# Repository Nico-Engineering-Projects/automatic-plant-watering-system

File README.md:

# Automatic Plant Watering System

An engineering project by Nico Gerber to develop an ESP32-based system that measures soil moisture and controls a water pump.

**Status:** In progress — breadboard assembly and development planning.

## Goal

Develop the hardware and firmware step by step, verify each stage, and document the design decisions, measurements and lessons learned.

## Current progress

- Relay and pump connected on the breadboard.
- ESP32 board selection, GPIO assignment, relay behaviour and electrical connections still need to be recorded and verified.
- Firmware development and functional testing are next.
- No watering performance or reliability results have been established yet.

## Planned development phases

- [ ] Verify ESP32 upload and Serial Monitor communication.
- [ ] Verify relay control and startup state with the pump disconnected.
- [ ] Verify a deliberately triggered short pump run with automatic shutoff.
- [ ] Measure and calibrate the soil-moisture sensor.
- [ ] Implement and test automatic watering with a soak period.
- [ ] Evaluate the results and document improvements.

## Planned software tools

- Visual Studio Code
- PlatformIO IDE
- Arduino framework for ESP32
- Git and GitHub for version history

The exact ESP32 board and GPIO configuration will be documented before the first firmware is added.

## Documentation

- [Development log](docs/development-log.md)
- Circuit diagrams, component list and test results will be added as the project progresses.
- The Word project report will be kept in `docs/`; a readable PDF can be included with major milestones.

## Project structure as the work grows

| Location | Contents |
| --- | --- |
| `README.md` | Current overview, status and setup instructions |
| `src/` | Firmware source, added when the PlatformIO project is created |
| `platformio.ini` | Verified board, framework and build configuration |
| `hardware/` | Wiring diagrams, schematics and parts list |
| `docs/` | Development log and project report |
| `results/` | Measurements and test observations |
| `images/` | Photographs of the actual project |

## Development history

Small changes are recorded as commits. Tags and releases will mark verified milestones. Each log entry should record what was actually tested and link to the relevant commit.

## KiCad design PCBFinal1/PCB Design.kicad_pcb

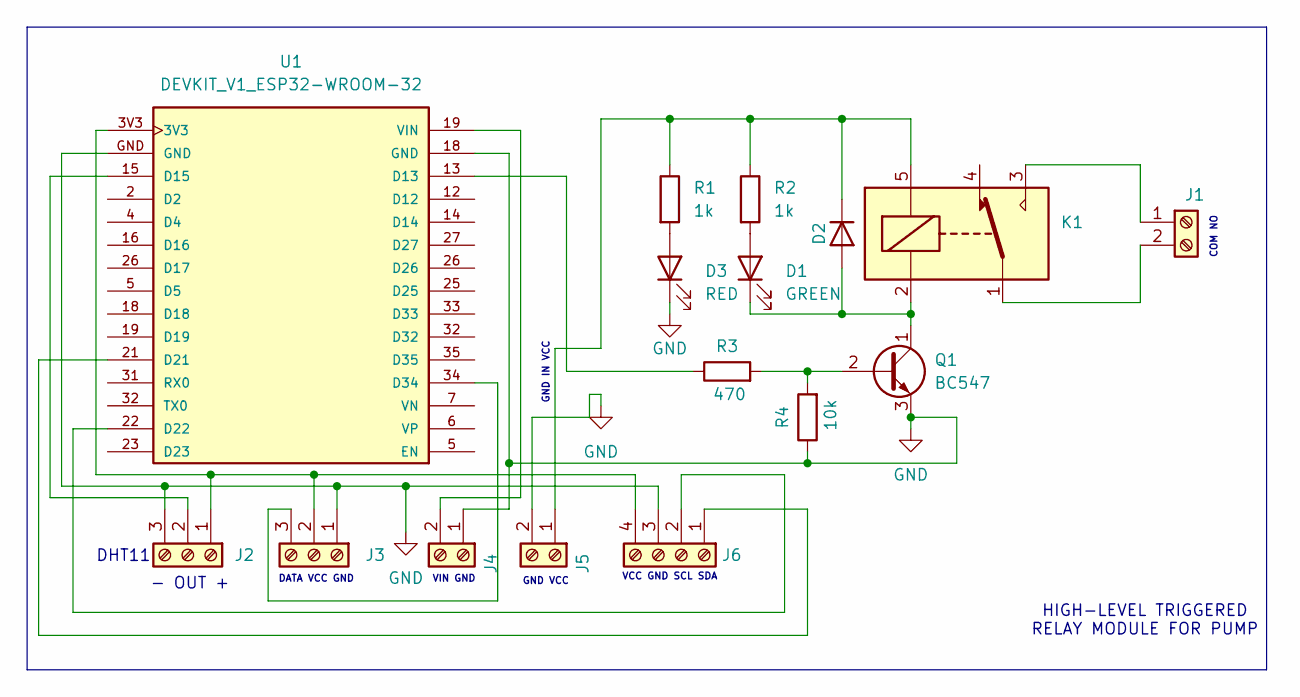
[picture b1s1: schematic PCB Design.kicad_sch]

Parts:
D1: GREEN; LED_D5.0mm
D2: 1N4007; D_DO-41_SOD81_P10.16mm_Horizontal
D3: RED; LED_D5.0mm
J1, J4, J5: Screw_Terminal_01x02; TerminalBlock_Phoenix_MKDS-1,5-2_1x02_P5.00mm_Horizontal
J2, J3: Screw_Terminal_01x03; TerminalBlock_Phoenix_MKDS-1,5-3-5.08_1x03_P5.08mm_Horizont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
J6: Screw_Terminal_01x04; TerminalBlock_Phoenix_MKDS-1,5-4-5.08_1x04_P5.08mm_Horizont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
K1: SANYOU_SRD_Form_C; Relay_SPDT_SANYOU_SRD_Series_Form_C
Q1: BC547; TO-92_Inline
R1, R2: 1k; R_Axial_DIN0207_L6.3mm_D2.5mm_P7.62mm_Horizontal
R3: 470; R_Axial_DIN0207_L6.3mm_D2.5mm_P7.62mm_Horizontal
R4: 10k; R_Axial_DIN0207_L6.3mm_D2.5mm_P7.62mm_Horizontal
U1: DEVKIT_V1_ESP32-WROOM-32; MODULE_DEVKIT_V1_ESP32-WROOM-32; PARTREV N/A

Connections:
GND: D3.1 (K), J2.3, J3.1, J4.1, J5.2, J6.3, Q1.3 (E), R4.1, U1.18 (GND), U1.GND
unnamed: D1.2 (A), R2.2
unnamed: D1.1 (K), D2.2 (A), K1.2, Q1.1 (C)
unnamed: D2.1 (K), J5.1, K1.5, R1.1, R2.1
unnamed: D3.2 (A), R1.2
unnamed: J1.1, K1.3
unnamed: J1.2, K1.1
unnamed: J2.1, J3.2, J6.4, U1.3V3
unnamed: J2.2, U1.15 (D15)
unnamed: J3.3, U1.34 (D34)
unnamed: J4.2, U1.19 (VIN)
unnamed: J6.1, U1.21 (D21)
unnamed: J6.2, U1.22 (D22)
unnamed: Q1.2 (B), R3.2, R4.2
unnamed: R3.1, U1.13 (D13)

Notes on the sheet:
DHT11
GND VCC
DATA VCC GND
GND IN VCC
COM NO
VIN GND
HIGH-LEVEL TRIGGERED RELAY MODULE FOR PUMP
VCC GND SCL SDA
- OUT +

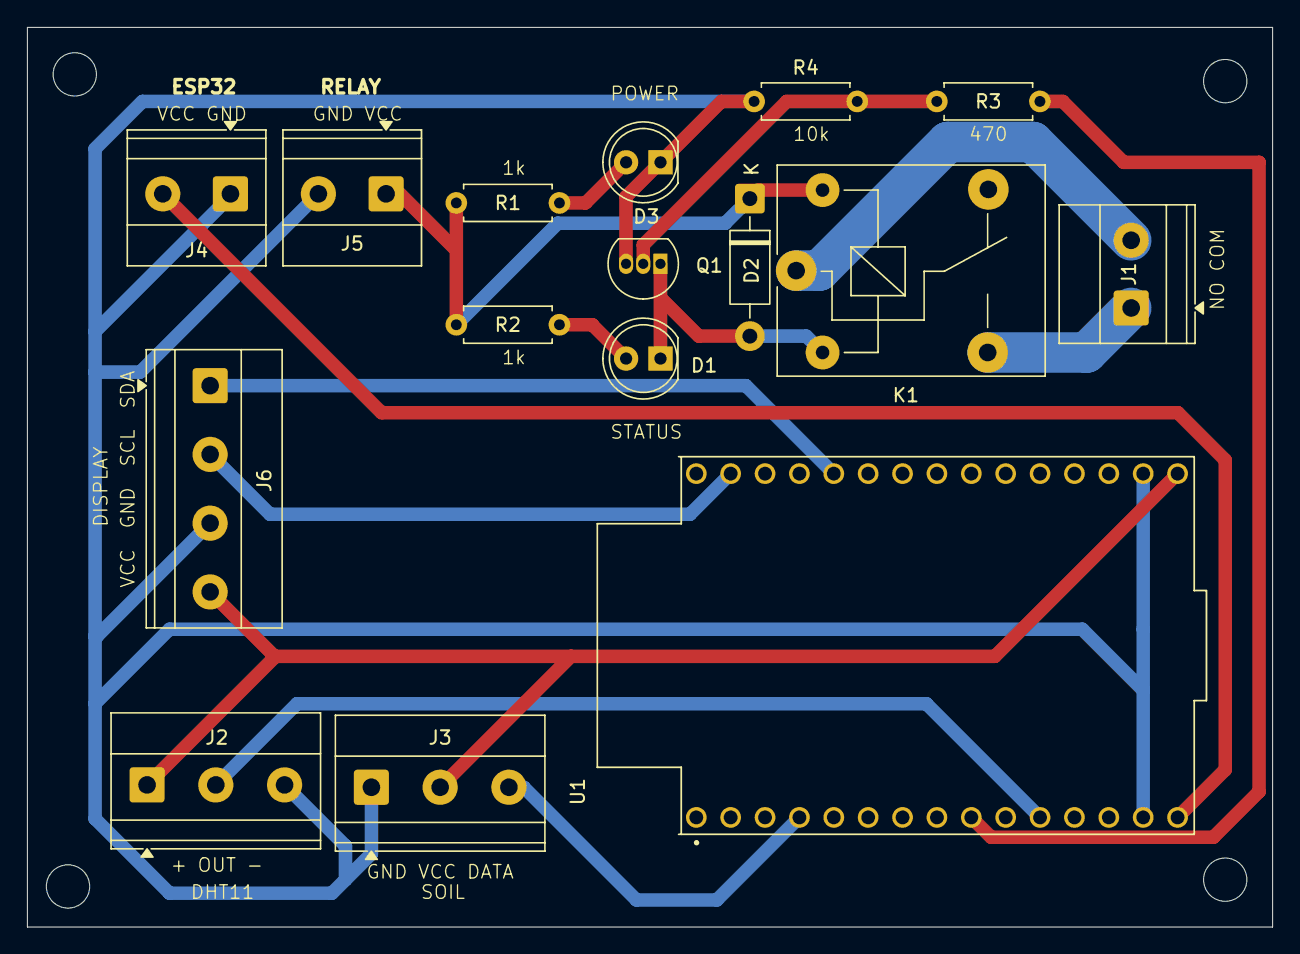
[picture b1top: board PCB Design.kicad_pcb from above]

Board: 2 copper layers, 92.0 x 66.5 mm, 16 parts (0 on the bottom side), 15 nets.
